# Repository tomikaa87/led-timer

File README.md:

# led-timer
Programmable timer for low voltage LED lights (e.g. christmas LED strings) with a Microchip PIC16.

**This project is in work-in-progress state**

# Features:
* Sophisticated scheduling system - you can choose from 48 individual 30 minute-length intervals to turn on the LED output
* Controllable LED brightness via PWM (Pulse Width Modulation) in 255 steps
* Dedicated LED driver circuit on the output
* Low power microcontroller - battery-friendly power consumption (LED output current not included)
  * 4 mA (screen on)
  * 0.2 mA (screen off)
  * ~6 μA (deep-sleep, only time-keeping) - more than 2 years from a standard CR2032 lithium battery
* Easy-to-use and intuitive user interface:
  * 3 buttons for changing settings, toggling the output etc.
  * OLED screen with schedule, output state, battery level indication and more
  * Each screen shows a legend for individual key functions
* Backup battery - timekeeping and changing settings work without external power

A custom-made PCB and a 3D-printable enclosure is still in development and should be published soon.

# Case

I've made a simple 3D-printable case in FreeCAD. It's a two-part design which can be assembled using M2 self-tapping screws.

# PCB

The first version of the PCB is a 4-layer design that can be manufactured for $2 at JLC PCB.
It's almost as small as the 0.96" SSD1306 OLED display module itself. Because different display modules have varying pinouts (VDD and GND swapped), the function of the first two pins are configurable via solder jumpers (JP1 and JP2).
The switch on the side can turn of the timer completely to conserve battery power while the timer is in storage.
The three buttons on the bottom are for navigation on the user interface.
The battery holder on the back side receives a standard CR2032 3V lithium cell.
The power input and LED output connectors are standard 2.54 mm pitch pin headers.

The interactive BOM can be accessed 

## 3D renders of the PCB

# Images of the prototype

## Main screen

## Main screen functions explained

## Settings screen

## Scheduler settings

## LED output brightness setting

## Clock setting

## Prototype setup

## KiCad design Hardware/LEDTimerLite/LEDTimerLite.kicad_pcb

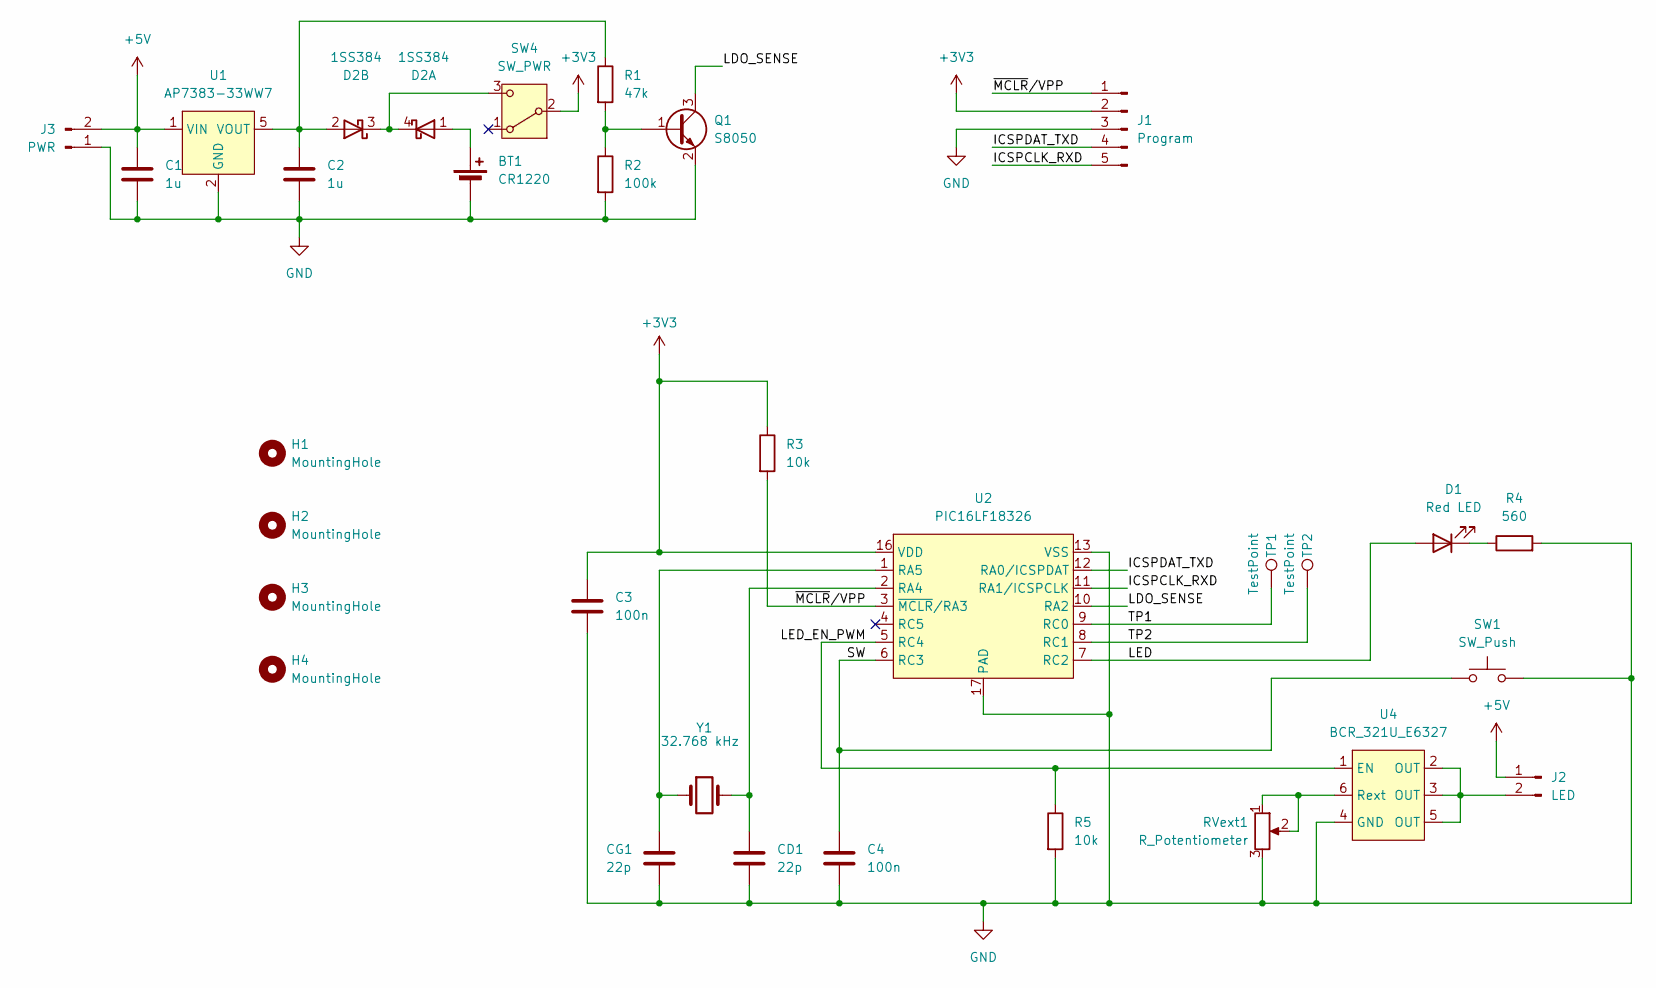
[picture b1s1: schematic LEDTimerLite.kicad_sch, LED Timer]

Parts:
BT1: CR1220; BatteryHolder_Keystone_3001_1x12mm; mouser part number 614-HU2032-LF; mouser description Coin Cell Battery Holders THRU HOLE FOR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
C1, C2: 1u; C_0805_2012Metric_Pad1.18x1.45mm_HandSolder
C3, C4: 100n; C_0805_2012Metric_Pad1.18x1.45mm_HandSolder
CD1: 22p; C_0805_2012Metric_Pad1.18x1.45mm_HandSolder
CG1: 22p; C_0805_2012Metric_Pad1.18x1.45mm_HandSolder
D1: Red LED; LED_0805_2012Metric_Pad1.15x1.40mm_HandSolder
D2: 1SS384; SOT-343_SC-70-4
H1, H2, H3, H4: MountingHole; MountingHole_2.2mm_M2_Pad_Via
J1: Program; PinHeader_1x05_P2.54mm_Vertical
J2: LED; PinHeader_1x02_P2.54mm_Horizontal
J3: PWR; PinHeader_1x02_P2.54mm_Horizontal
Q1: S8050; SOT-23
R1: 47k; R_0805_2012Metric_Pad1.20x1.40mm_HandSolder
R2: 100k; R_0805_2012Metric_Pad1.20x1.40mm_HandSolder
R3, R5: 10k; R_0805_2012Metric_Pad1.20x1.40mm_HandSolder
R4: 560; R_0805_2012Metric_Pad1.20x1.40mm_HandSolder
RVext1: R_Potentiometer; Potentiometer_Bourns_TC33X_Vertical
SW1: SW_Push; SW_SPST_TL3305A
SW4: SW_PWR; 1825232-1
TP1, TP2: TestPoint; TestPoint_Pad_D1.5mm
U1: AP7383-33WW7; SOT-23-5
U2: PIC16LF18326; UQFN-16-1EP_4x4mm_P0.65mm_EP2.6x2.6mm
U4: BCR_321U_E6327; SC-74-6_1.55x2.9mm_P0.95mm
Y1: 32.768 kHz; Crystal_SMD_MicroCrystal_CC8V-T1A-2Pin_2.0x1.2mm_HandSolder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

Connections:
+3V3: C3.1, J1.2, R3.1, SW4.2 (B), U2.16 (VDD)
+5V: C1.1, J2.1, J3.2, U1.1 (VIN)
/ICSPCLK_RXD: J1.5, U2.11 (RA1/ICSPCLK)
/ICSPDAT_TXD: J1.4, U2.12 (RA0/ICSPDAT)
/LDO_SENSE: Q1.3 (C), U2.10 (RA2)
/LED: D1.2 (A), U2.7 (RC2)
/LED_EN_PWM: R5.1, U2.5 (RC4), U4.1 (EN)
/SW: C4.1, SW1.2, U2.6 (RC3)
/TP1: TP1.1, U2.9 (RC0)
/TP2: TP2.1, U2.8 (RC1)
/~MCLR/VPP: J1.1, R3.2, U2.3 (~MCLR/RA3)
GND: BT1.2 (-), C1.2, C2.2, C3.2, C4.2, CD1.2, CG1.2, J1.3, J3.1, Q1.2 (E), R2.2, R4.2, R5.2, RVext1.3, SW1.1, U1.2 (GND), U2.13 (VSS), U2.17 (PAD), U4.4 (GND)
unnamed: BT1.1 (+), D2.1 (A)
unnamed: D1.1 (K), R4.1
unnamed: D2.3 (K), D2.4 (K), SW4.3 (C)
unnamed: C2.1, D2.2 (A), R1.1, U1.5 (VOUT)
unnamed: J2.2, U4.2 (OUT), U4.3 (OUT), U4.5 (OUT)
unnamed: Q1.1 (B), R1.2, R2.1
unnamed: CD1.1, U2.2 (RA4), Y1.2
unnamed: CG1.1, U2.1 (RA5), Y1.1
unnamed: RVext1.1, RVext1.2, U4.6 (Rext)

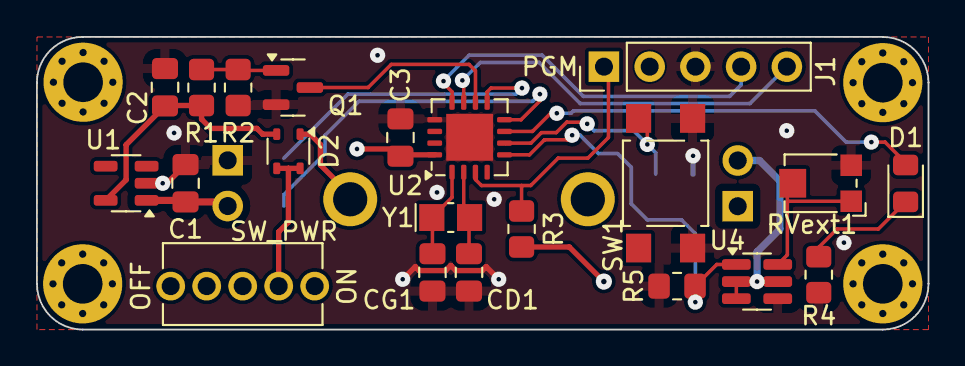
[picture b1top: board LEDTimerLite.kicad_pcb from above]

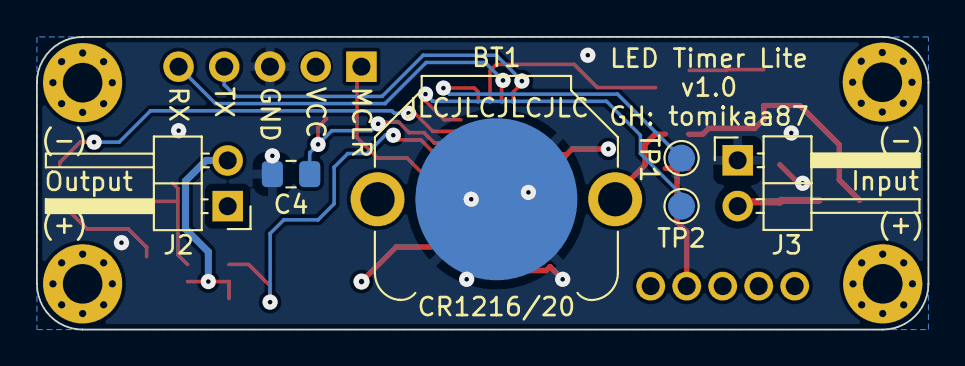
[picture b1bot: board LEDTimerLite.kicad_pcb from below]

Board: 4 copper layers, 49.5 x 16.3 mm, 31 parts (6 on the bottom side), 21 nets.

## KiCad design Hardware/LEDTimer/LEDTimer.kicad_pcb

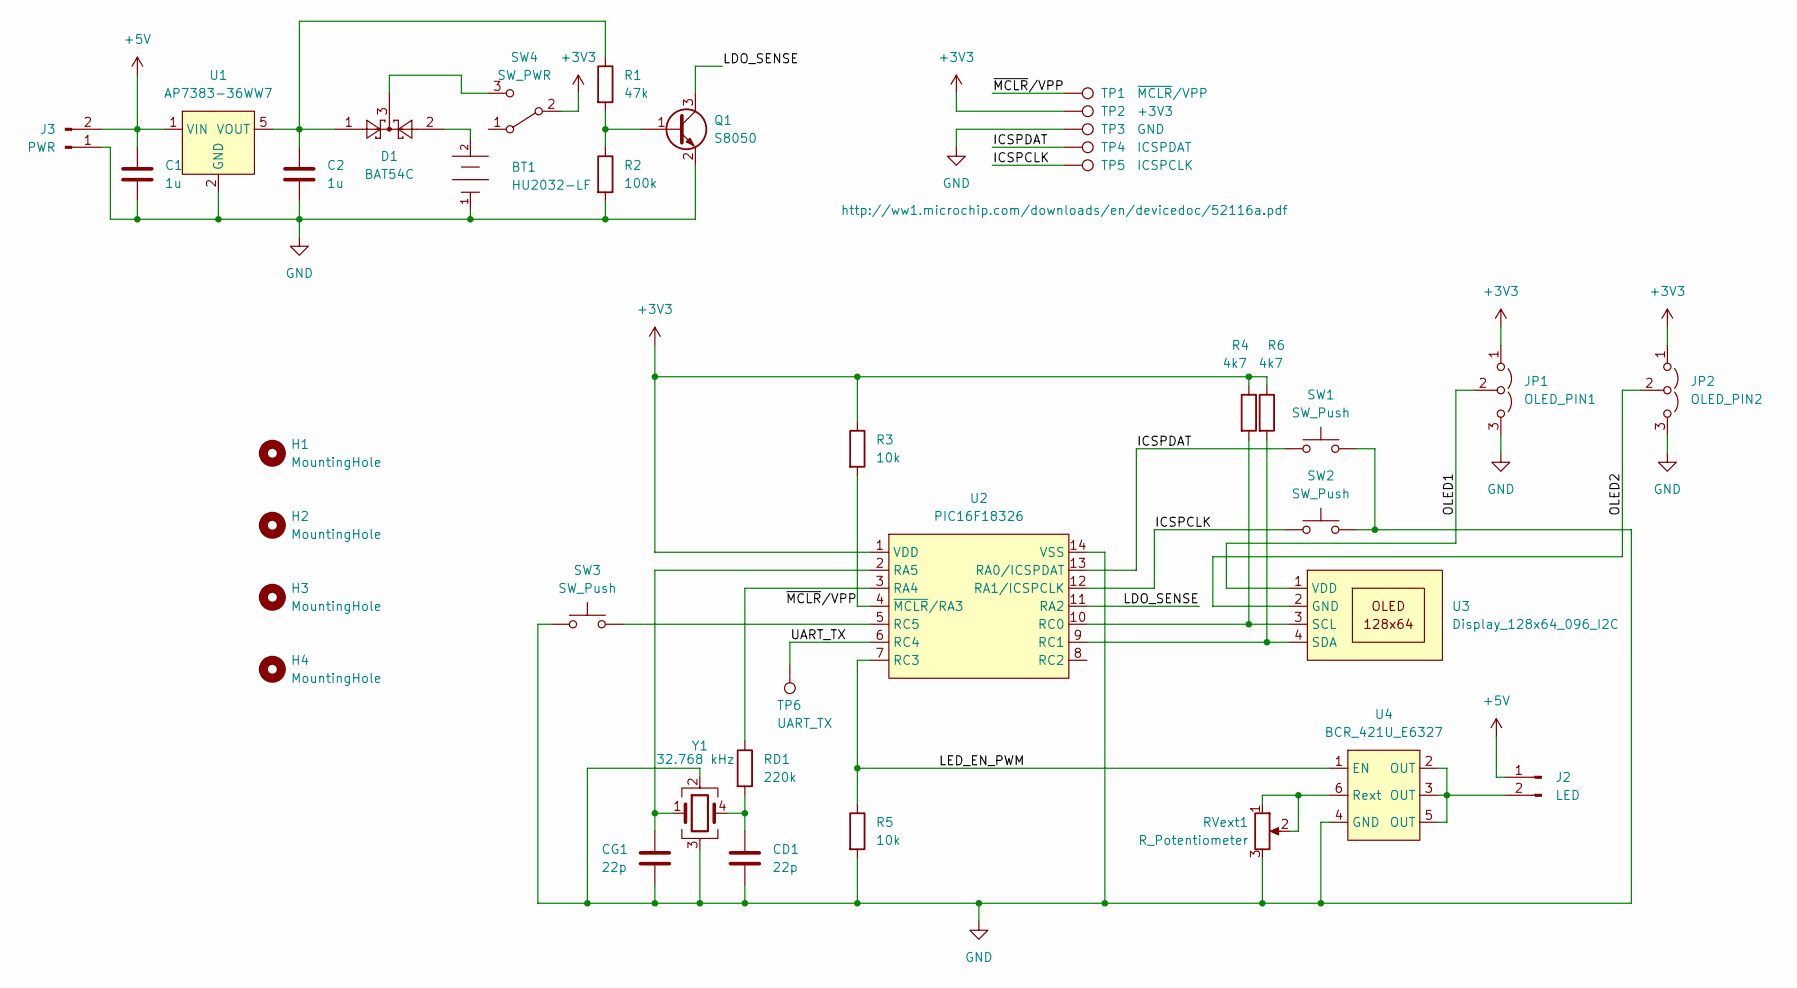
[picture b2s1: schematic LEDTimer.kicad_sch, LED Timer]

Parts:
BT1: HU2032-LF; Renata-HU2032-LF-0-0-0; mouser part number 614-HU2032-LF; mouser description Coin Cell Battery Holders THRU HOLE FOR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
C1, C2: 1u; C_0805_2012Metric_Pad1.18x1.45mm_HandSolder
CD1: 22p; C_0805_2012Metric_Pad1.18x1.45mm_HandSolder
CG1: 22p; C_0805_2012Metric_Pad1.18x1.45mm_HandSolder
D1: BAT54C; SOT-416
H1, H2, H3, H4: MountingHole; MountingHole_2.2mm_M2
J2: LED; PinHeader_1x02_P2.54mm_Horizontal
J3: PWR; PinHeader_1x02_P2.54mm_Horizontal
JP1: OLED_PIN1; SolderJumper-3_P1.3mm_Open_RoundedPad1.0x1.5mm
JP2: OLED_PIN2; SolderJumper-3_P1.3mm_Open_RoundedPad1.0x1.5mm
Q1: S8050; SOT-23
R1: 47k; R_0805_2012Metric_Pad1.20x1.40mm_HandSolder
R2: 100k; R_0805_2012Metric_Pad1.20x1.40mm_HandSolder
R3, R5: 10k; R_0805_2012Metric_Pad1.20x1.40mm_HandSolder
R4, R6: 4k7; R_0805_2012Metric_Pad1.20x1.40mm_HandSolder
RD1: 220k; R_0805_2012Metric_Pad1.20x1.40mm_HandSolder
RVext1: R_Potentiometer; Potentiometer_Vishay_TS53YJ_Vertical
SW1, SW2, SW3: SW_Push; EVQ9P701P
SW4: SW_PWR; 1825232-1
TP1: ~{MCLR}/VPP; TestPoint_Pad_D1.5mm
TP2: +3V3; TestPoint_Pad_D1.5mm
TP3: GND; TestPoint_Pad_D1.5mm
TP4: ICSPDAT; TestPoint_Pad_D1.5mm
TP5: ICSPCLK; TestPoint_Pad_D1.5mm
TP6: UART_TX; TestPoint_Pad_D1.5mm
U1: AP7383-36WW7; SOT-23-5
U2: PIC16F18326; SOIC-14_3.9x8.7mm_P1.27mm
U3: Display_128x64_096_I2C
U4: BCR_421U_E6327; SC-74-6_1.5x2.9mm_P0.95mm
Y1: 32.768 kHz; Crystal_SMD_Abracon_ABS25-4Pin_8.0x3.8mm

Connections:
+3V3: JP1.1 (A), JP2.1 (A), R3.1, R4.1, R6.1, SW4.2 (B), TP2.1, U2.1 (VDD)
+5V: C1.1, J2.1, J3.2, U1.1 (VIN)
/ICSPCLK: SW2.2, TP5.1, U2.12 (RA1/ICSPCLK)
/ICSPDAT: SW1.2, TP4.1, U2.13 (RA0/ICSPDAT)
/LDO_SENSE: Q1.3 (C), U2.11 (RA2)
/LED_EN_PWM: R5.1, U2.7 (RC3), U4.1 (EN)
/OLED1: JP1.2 (C), U3.1 (VDD)
/OLED2: JP2.2 (C), U3.2 (GND)
/UART_TX: TP6.1, U2.6 (RC4)
/~MCLR/VPP: R3.2, TP1.1, U2.4 (~MCLR/RA3)
GND: BT1.1 (CATHODE), C1.2, C2.2, CD1.2, CG1.2, J3.1, JP1.3 (B), JP2.3 (B), Q1.2 (E), R2.2, R5.2, RVext1.3, SW1.1, SW2.1, SW3.1, TP3.1, U1.2 (GND), U2.14 (VSS), U4.4 (GND), Y1.2, Y1.3
unnamed: BT1.2 (ANODE), D1.2
unnamed: C2.1, D1.1, R1.1, U1.5 (VOUT)
unnamed: CD1.1, RD1.2, Y1.4
unnamed: CG1.1, U2.2 (RA5), Y1.1
unnamed: D1.3, SW4.3 (C)
unnamed: J2.2, U4.2 (OUT), U4.3 (OUT), U4.5 (OUT)
unnamed: Q1.1 (B), R1.2, R2.1
unnamed: R4.2, U2.10 (RC0), U3.3 (SCL)
unnamed: R6.2, U2.9 (RC1), U3.4 (SDA)
unnamed: RD1.1, U2.3 (RA4)
unnamed: RVext1.1, RVext1.2, U4.6 (Rext)
unnamed: SW3.2, U2.5 (RC5)

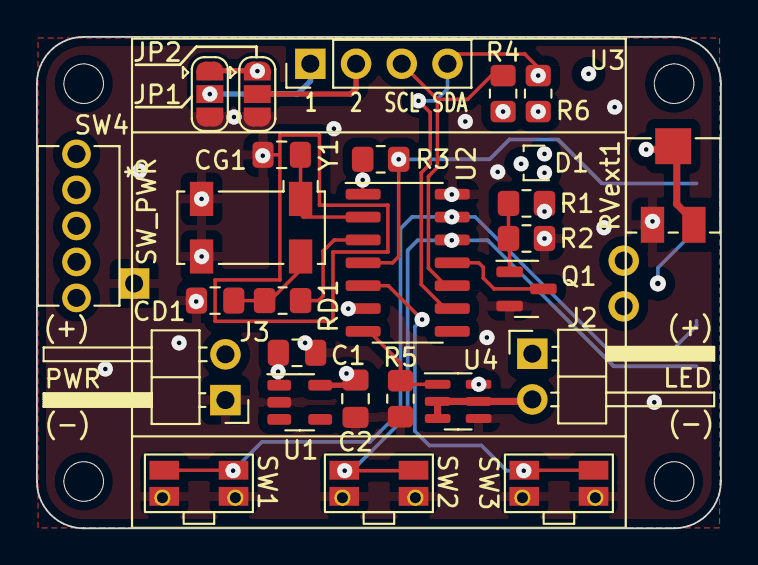
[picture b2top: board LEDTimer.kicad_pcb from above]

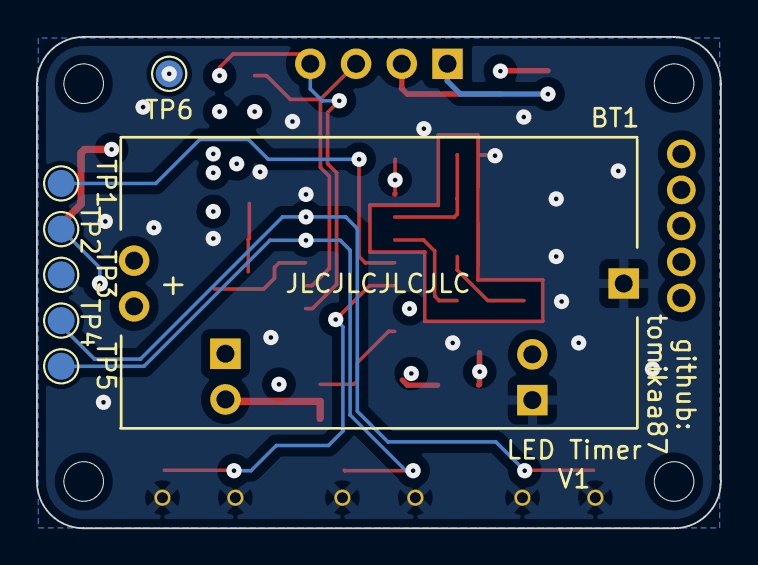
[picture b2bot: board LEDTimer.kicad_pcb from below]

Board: 4 copper layers, 38.0 x 27.3 mm, 38 parts (7 on the bottom side), 23 nets.

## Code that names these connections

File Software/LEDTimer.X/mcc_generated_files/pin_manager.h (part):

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// get/set IO_SW1 aliases
#define IO_SW1_TRIS                 TRISAbits.TRISA0
#define IO_SW1_LAT                  LATAbits.LATA0
#define IO_SW1_PORT                 PORTAbits.RA0
#define IO_SW1_WPU                  WPUAbits.WPUA0
#define IO_SW1_OD                   ODCONAbits.ODCA0
#define IO_SW1_ANS                  ANSELAbits.ANSA0
#define IO_SW1_SetHigh()            do { LATAbits.LATA0 = 1; } while(0)
#define IO_SW1_SetLow()             do { LATAbits.LATA0 = 0; } while(0)
#define IO_SW1_Toggle()             do { LATAbits.LATA0 = ~LATAbits.LATA0; } while(0)
#define IO_SW1_GetValue()           PORTAbits.RA0
#define IO_SW1_SetDigitalInput()    do { TRISAbits.TRISA0 = 1; } while(0)
#define IO_SW1_SetDigitalOutput()   do { TRISAbits.TRISA0 = 0; } while(0)
#define IO_SW1_SetPullup()          do { WPUAbits.WPUA0 = 1; } while(0)
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// get/set IO_SW2 aliases
#define IO_SW2_TRIS                 TRISAbits.TRISA1
#define IO_SW2_LAT                  LATAbits.LATA1
#define IO_SW2_PORT                 PORTAbits.RA1
#define IO_SW2_WPU                  WPUAbits.WPUA1
#define IO_SW2_OD                   ODCONAbits.ODCA1
#define IO_SW2_ANS                  ANSELAbits.ANSA1
#define IO_SW2_SetHigh()            do { LATAbits.LATA1 = 1; } while(0)
#define IO_SW2_SetLow()             do { LATAbits.LATA1 = 0; } while(0)
#define IO_SW2_Toggle()             do { LATAbits.LATA1 = ~LATAbits.LATA1; } while(0)
#define IO_SW2_GetValue()           PORTAbits.RA1
#define IO_SW2_SetDigitalInput()    do { TRISAbits.TRISA1 = 1; } while(0)
#define IO_SW2_SetDigitalOutput()   do { TRISAbits.TRISA1 = 0; } while(0)
#define IO_SW2_SetPullup()          do { WPUAbits.WPUA1 = 1; } while(0)
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// get/set IO_LDO_SENSE aliases
#define IO_LDO_SENSE_TRIS                 TRISAbits.TRISA2
#define IO_LDO_SENSE_LAT                  LATAbits.LATA2
#define IO_LDO_SENSE_PORT                 PORTAbits.RA2
#define IO_LDO_SENSE_WPU                  WPUAbits.WPUA2
#define IO_LDO_SENSE_OD                   ODCONAbits.ODCA2
#define IO_LDO_SENSE_ANS                  ANSELAbits.ANSA2
#define IO_LDO_SENSE_SetHigh()            do { LATAbits.LATA2 = 1; } while(0)
#define IO_LDO_SENSE_SetLow()             do { LATAbits.LATA2 = 0; } while(0)
#define IO_LDO_SENSE_Toggle()             do { LATAbits.LATA2 = ~LATAbits.LATA2; } while(0)
#define IO_LDO_SENSE_GetValue()           PORTAbits.RA2
#define IO_LDO_SENSE_SetDigitalInput()    do { TRISAbits.TRISA2 = 1; } while(0)
#define IO_LDO_SENSE_SetDigitalOutput()   do { TRISAbits.TRISA2 = 0; } while(0)
#define IO_LDO_SENSE_SetPullup()          do { WPUAbits.WPUA2 = 1; } while(0)
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#define RC0_SetHigh()            do { LATCbits.LATC0 = 1; } while(0)
#define RC0_SetLow()             do { LATCbits.LATC0 = 0; } while(0)
#define RC0_Toggle()             do { LATCbits.LATC0 = ~LATCbits.LATC0; } while(0)
#define RC0_GetValue()              PORTCbits.RC0
#define RC0_SetDigitalInput()    do { TRISCbits.TRISC0 = 1; } while(0)
#define RC0_SetDigitalOutput()   do { TRISCbits.TRISC0 = 0; } while(0)
#define RC0_SetPullup()             do { WPUCbits.WPUC0 = 1; } while(0)
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#define RC1_SetHigh()            do { LATCbits.LATC1 = 1; } while(0)
#define RC1_SetLow()             do { LATCbits.LATC1 = 0; } while(0)
#define RC1_Toggle()             do { LATCbits.LATC1 = ~LATCbits.LATC1; } while(0)
#define RC1_GetValue()              PORTCbits.RC1
#define RC1_SetDigitalInput()    do { TRISCbits.TRISC1 = 1; } while(0)
#define RC1_SetDigitalOutput()   do { TRISCbits.TRISC1 = 0; } while(0)
#define RC1_SetPullup()             do { WPUCbits.WPUC1 = 1; } while(0)
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#define RC3_SetHigh()            do { LATCbits.LATC3 = 1; } while(0)
#define RC3_SetLow()             do { LATCbits.LATC3 = 0; } while(0)
#define RC3_Toggle()             do { LATCbits.LATC3 = ~LATCbits.LATC3; } while(0)
#define RC3_GetValue()              PORTCbits.RC3
#define RC3_SetDigitalInput()    do { TRISCbits.TRISC3 = 1; } while(0)
#define RC3_SetDigitalOutput()   do { TRISCbits.TRISC3 = 0; } while(0)
#define RC3_SetPullup()             do { WPUCbits.WPUC3 = 1; } while(0)
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#define RC4_SetHigh()            do { LATCbits.LATC4 = 1; } while(0)
#define RC4_SetLow()             do { LATCbits.LATC4 = 0; } while(0)
#define RC4_Toggle()             do { LATCbits.LATC4 = ~LATCbits.LATC4; } while(0)
#define RC4_GetValue()              PORTCbits.RC4
#define RC4_SetDigitalInput()    do { TRISCbits.TRISC4 = 1; } while(0)
#define RC4_SetDigitalOutput()   do { TRISCbits.TRISC4 = 0; } while(0)
#define RC4_SetPullup()             do { WPUCbits.WPUC4 = 1; } while(0)
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// get/set IO_SW3 aliases
#define IO_SW3_TRIS                 TRISCbits.TRISC5
#define IO_SW3_LAT                  LATCbits.LATC5
#define IO_SW3_PORT                 PORTCbits.RC5
#define IO_SW3_WPU                  WPUCbits.WPUC5
#define IO_SW3_OD                   ODCONCbits.ODCC5
#define IO_SW3_ANS                  ANSELCbits.ANSC5
#define IO_SW3_SetHigh()            do { LATCbits.LATC5 = 1; } while(0)
#define IO_SW3_SetLow()             do { LATCbits.LATC5 = 0; } while(0)
#define IO_SW3_Toggle()             do { LATCbits.LATC5 = ~LATCbits.LATC5; } while(0)
#define IO_SW3_GetValue()           PORTCbits.RC5
#define IO_SW3_SetDigitalInput()    do { TRISCbits.TRISC5 = 1; } while(0)
#define IO_SW3_SetDigitalOutput()   do { TRISCbits.TRISC5 = 0; } while(0)
#define IO_SW3_SetPullup()          do { WPUCbits.WPUC5 = 1; } while(0)
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
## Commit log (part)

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2022-12-01 Initial comit
2022-12-01 Add PCB design files
2022-12-01 Ignore macOS-generated files
2022-12-02 Set system clock speed to 16 MHz
2022-12-02 Move system-related logic into System
2022-12-02 Add option to invert text and graphics
2022-12-02 Implement high-resolution fast-tick system
2022-12-02 Implement keypad handling logic
2022-12-02 Implement keypad de-bouncing logic
2022-12-02 Clean the backroung when drawing a text
2022-12-02 Fix background drawing of texts
2022-12-02 Handle keys in UI, implement auto display power control
2022-12-03 Initial commit of Main screen
2022-12-03 Add LED activity indicator icon
2022-12-03 Add external power indicator
2022-12-04 Fix the clock and the segment indicator on the main screen
2022-12-04 Avoid display artifacts on battery
2022-12-04 Properly initialize the screen after startup and keep the MCU awake
2022-12-04 Update the resistor values of the LDO_SENSE divider
2022-12-04 Automatic code reformat
2022-12-04 Use proper function prototypes in the headers
2022-12-04 Implement battery voltage measurement and power input switchover detection
2022-12-04 Suppress a bunch of uninteresting compiler warnings
2022-12-04 Workaround a potential stack overflow in main()
2022-12-04 Clean up the interface of System
2022-12-04 Handle power input changes properly
2022-12-04 Add missing values to I2C pull-up resistors
2022-12-04 Conserve more power by turning off the FVR in sleep mode
2022-12-04 MCC config keeps changing for some reason...
2022-12-04 Initial commit of Settings
2022-12-04 Free up some program space
2022-12-05 Optimize the code to avoid potential stack overflows, centralize the config
2022-12-06 Start implementing the keypad logic from pic-thermostat
2022-12-06 Improve key handling logic in UI
2022-12-06 Remove extra new lines from UI logs
2022-12-06 Implement OutputController, add output toggle function to the Main screen
2022-12-07 Implement loading/saving settings
2022-12-07 Implement functions for schedule data manipulation
2022-12-09 Handle output toggling in Main screen logic
2022-12-09 Add function to initialize settings data with default values
2022-12-09 Implement page switching logic in Settings screen
2022-12-10 Implement settings, update main screen key help bar
2022-12-10 Implement splash screen
2022-12-10 Update battery indicator after starting up from battery
2022-12-10 Update VDD reading immediately after startup
2022-12-10 Turn off the display before going into sleep mode
2022-12-10 Add feature description to Readme
2022-12-10 Implement clock settings
2022-12-10 Add prototype images
2022-12-10 Add more prototype images
2022-12-10 Add images of the prototype
2022-12-10 Add image of the prototype setup
2022-12-10 Add PCB and enclosuse info to Readme
2022-12-10 Fix missing clock setting title
2022-12-13 PCB: add footprint libraries
2022-12-13 Change system clocl to 16 Mhz
2022-12-13 Add datasheets
2022-12-13 PCB: start laying out the board
2022-12-13 Add setting for display brightness
2022-12-14 PCB: first version of the layout
2022-12-15 Add compiler include directory to fix code assistant on mac
2022-12-17 Set RTC seconds to 0 when changing the time
2022-12-20 Add compiler include directory to fix code assistant on linux
2022-12-20 Convert all line endings to LF
2022-12-21 Disable debug mode by default
2022-12-21 PCB: new layout (not routed yet)
2022-12-21 PCB: update and add new models
2022-12-21 PCB: move the switches closer to the edge
2022-12-22 PCB: use a 4-layer design
2022-12-22 PCB: fix DRC issues
2022-12-22 PCB: flip the power input connector
2022-12-27 PCB: re-purpose the switch as main power switch, add a transistor to LDO_SENSE for protection
2022-12-28 PCB: add interactive BOM
2022-12-28 PCB: 3D renders
2022-12-28 Add PCB details to README
2022-12-28 Fix README typos
2022-12-28 PCB: add pull-down resistor to LED_EN_PWM
2022-12-28 Switch to PIC16F18326
2022-12-28 Fix issues and warnings after PIC transition
2022-12-28 Fix output pin mapping
2022-12-28 Bump version
2022-12-28 PCB: swap the MCU to 16F18326
2022-12-28 Update estimated sleep power consumption and battery life in README
2022-12-28 Tweak the config, disable unused peripherals
2022-12-28 Tweak the config, set the default PWM5 DC value to 0
2023-01-01 PCB: adjust the footprint of RVext1
2023-01-02 Case: start designing the case
2023-01-02 Case: add cut-outs for the buttons
2023-01-02 Case: adjust button cut-outs to be 3D-printable
2023-01-02 Case: add cut-outs for the connectors and the trimmer
2023-01-02 Case: add the bottom part
2023-01-02 Case: finish the bottom part
2023-01-02 Case: add preview images
2023-01-02 Add preview images of the case to the Readme
2023-01-02 Fix broken image link in the Readme
2023-01-14 Fix issues with PIC16F18326
2023-01-18 Update VBatDiodeDropMilliVolts for BAT54C
2023-01-18 Use FVREN instead of FVRMD to preserve FVR SFRs
2023-01-18 Update IBOM
2023-01-19 Improve and clean-up the output contol logic
2023-01-19 Remove unnecessary reserved field
2023-01-19 Fix data EE handling routines
2023-01-19 Fix the scheduler logic in the output controller
2023-01-19 Decrease I2C speed to standard 400 kHz
2023-01-19 Add reset reason indicator to the splash screen
2023-01-19 Disable BOR since it triggers unnecessarily on some devices
2023-01-19 Fix Types_getScheduleSegmentBit() to return a binary value
2023-01-19 Update the screen immediately when the output state changes
2023-01-19 Update the output toggle key help icon set
2023-01-21 Update deep-sleep consumption and battery life
2023-01-21 Enable VREGPM to conserve more power in sleep mode
2023-01-21 Optimize background clearing of power indicator, wake the screen on power input change
2023-01-29 Change CLib to C90 (needed for 24-bit FP types)
2023-01-29 Implement sunrise/sunset calculation
2023-01-29 Add info header to SunriseSunset
2023-01-29 Print test sunrise/sunset data on the splash screen
2023-01-30 Implement new scheduling options
2023-01-31 Continue implementing the new scheduler settings
2023-01-31 Start implementing a new menu screen
2023-01-31 Implement generic graphics primitives for screen drawing
2023-01-31 Main screen facelift
2023-01-31 Migrate old settings to the new pages
2023-01-31 Add gimp project for icon-set
2023-02-13 Add Date settings screen
2023-02-14 Add OLED display tweaks for larger screens
2023-02-15 Improve Date settings screen
2023-02-15 Implement RTC calendar
2023-02-17 Fix location setting issues, bump version
2023-02-17 Add isLeapYear to Clock
2023-02-19 Add design file for LED toggle indicator
2023-02-19 Automatically update sunrise/sunset time
2023-02-19 Optimize a bit with pre-calculated values
2023-02-19 Optimize CRC check in Settings
2023-02-19 Optimize loops
2023-02-20 Add time zone settings screen, update time settings screen
2023-02-20 Update selection change icons in settings
2023-02-20 Optimize a little bit more in the OLED driver
2023-02-20 Optimize showStartupScreen
2023-02-20 Optimize/de-duplicate string literals
2023-02-26 Add generator for sunrise/sunset LUT
2023-02-26 Use LUT for sunrise/sunset calculation
2023-02-26 Clarify time zone of LUT timestamps
2023-03-11 Scheduler screen: implement selection change and adjustment logic
2023-03-11 Scheduler screen: fix selection and drawing issues
2023-03-12 Scheduler screen: add remaining labels
2023-03-12 Add build config for sunrise/sunset LUT
2023-03-12 Add build config for sunrise/sunset calculation
2023-03-14 Implement settings for multi-schedule interval timer
2023-03-14 Integrate interval scheduler in OutputController
2023-03-15 Add active/inactive flag to interval schedule
2023-03-15 Build SunriseSunset_Calc with -Os
2023-03-15 Optimize drawing
2023-03-15 Use graphics pattern instead of settings icon
2023-03-15 Remove redundant mini bulb icon
2023-03-15 Use single bitmap for screen title end caps
2023-03-15 Fix segment scheduler indicator bar drawing issues
2023-03-15 Add icon design for sunrise/sunset
2023-03-15 Fix drawing and layout issues of scheduler settings screen
2023-04-02 Add LedTimerSchedulerPlayground
2023-04-02 Add typedef Clock_Time
2023-04-02 Fix GitHub directory in LedTimerSchedulerPlayground
2023-04-02 Show info about the next schedule transition on the main screen
2023-04-02 Show sunrise/sunset info on the main screen
2023-04-02 Fix day-of-year and time-zone-based calculations
2023-04-06 Update DFP
2023-04-06 Remove unused files
2023-04-06 Add date utils
2023-04-06 Replace memset() calls to spare flash space
2023-04-06 Optimize flash usage of Graphics_DrawScreenTitle
2023-04-06 Optimize flash usage of Graphics_DrawKeypadHelpBar
2023-04-06 Fix drawing bitmaps touching screen's right edge
2023-04-06 Put parentheses around macro parameters
2023-04-06 Re-style interval schedule indicator
2023-04-06 Fix behavior of SSD1306_SEND_FLIPX
2023-04-06 Fix non-updating switch type on schedule index change
2023-04-06 Start developing a generic DST check algorithm
2023-04-06 Start developing DST settings screen
2023-04-17 Researching DST calculation
2023-04-17 Optimize lastDayOfMonth calculation
2023-06-01 Case: update button design (WIP)
2023-06-05 Case: update front piece design to make buttons usable
2023-06-05 Case: add factory files
2023-06-05 Case: adjust part positions
2023-06-05 Add adjustment logic to DST settings screen
2023-06-05 Add new case images
2023-06-05 Add UTC/Local flag to DST settings
2023-06-10 LedTimerSchedulerPlayground: add GetNextTransitionV2
2023-06-10 Add experimental CMake project file
2023-06-10 Update .gitignore for VSCode
2023-06-10 Add functions for DST calculation
2023-06-10 Use one DST Data struct
2023-11-26 Reduce OLED contrast on battery
2024-10-01 Optimize sprintf usage
    Reduce program space usage by limiting sprintf
    format specifiers to %u and %c.
2024-10-01 Reduce LUT size by 50%
    By limiting the precision to 6 minute "buckets",
    sunrise and sunset times can be stored on 8 bits
    instead of 16 bits.
2024-10-01 Fix text formatting issues on main screen
2024-10-01 Fix text formatting issues on DST settings screen
2024-10-01 Bump version to 2.2.0
2024-10-02 Switch to C calendar API
2024-10-02 Switch to XC8 v2.49 FuSa
    This compiler generates the smallest code so far.
    It's also a Functional Safety version.
2024-12-09 Add LED Timer Lite
2024-12-10 LTL: try new PCB layout
2024-12-12 LTL: improve track routing
2024-12-13 LTL: replace BAT54C with 1SS384 (lower Vf)
2024-12-13 LTL: fix ERC issues
2024-12-13 LTL: fix DRC issues
2024-12-13 LTL: add extra test points, optimize layout
2024-12-13 LTL: replace LED driver and RVext1
    Use BCR321U (250 mA) instead of BCR421U (150 mA).
    Use TC33X-2-101E as RVext1 because it's cheaper.
2024-12-15 LTL: remove MCC
2024-12-16 LTL: add debouncing capacitor to SW
2024-12-16 LTL: make basic components work
2024-12-17 LTL: fix sleeping
2024-12-18 LTL: clean up system init, reduce Fosc to 8 MHz
2024-12-22 LTL: rename task() to runTasks()
2024-12-22 LTL: do VDD measurement during sleep
2024-12-22 LTL: implement indicator LED control logic
2024-12-22 LTL: cleanup main.c
2024-12-23 LTL: implement input parsing in ProgrammingInterface
2024-12-23 LTL: add PI packet format ideas
2024-12-30 LTL: implement PI packet parser
2024-12-30 LTL: implement PI field count check
2024-12-31 LTL: implement PI TIME and DATE field parsing
2025-01-01 LTL: implement PI all the command parsers
2025-01-01 LTL: cleanup PI, implement output control
2025-01-01 LTL: add PI command to set scheduler type
2025-01-01 LTL: clarify PI SCHINT offset fields
2025-01-02 LTL: cleanup Clock's timer code
2025-01-02 LTL: use unique context names to ease debugging
2025-02-23 Implement key remapping for debugging
2025-02-23 Fix date and time handling issues
2025-02-23 Disable unnecessary features
2025-02-23 Add option to omit LUT for debugging
2025-02-25 Implement gentle brightness ramp up logic
2025-02-25 Preview LED brightness in settings
2025-02-25 Update project configuration
2025-02-26 Replace sprintf with uint16ToString
2025-02-26 Increase output PWM resolution
2025-02-26 Generated code cleanup
2025-02-26 Update build configurations: compiler, DFP
2025-02-26 Remove unnecessary casts
2025-02-26 Slow down brightness ramp up
2025-11-24 Update DFP and compiler

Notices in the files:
Software/LEDTimer.X/mcc_generated_files/pin_manager.h:
(c) 2018 Microchip Technology Inc. and its subsidiaries.
parts and their libraries:
Copyright 2021 Accelerated Designs. All rights reserved.
